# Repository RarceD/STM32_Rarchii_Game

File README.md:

# STM32_Rarchii_Game
This is a simple aproach to the stm32 developer tools and hardware design for one of this low power uC.

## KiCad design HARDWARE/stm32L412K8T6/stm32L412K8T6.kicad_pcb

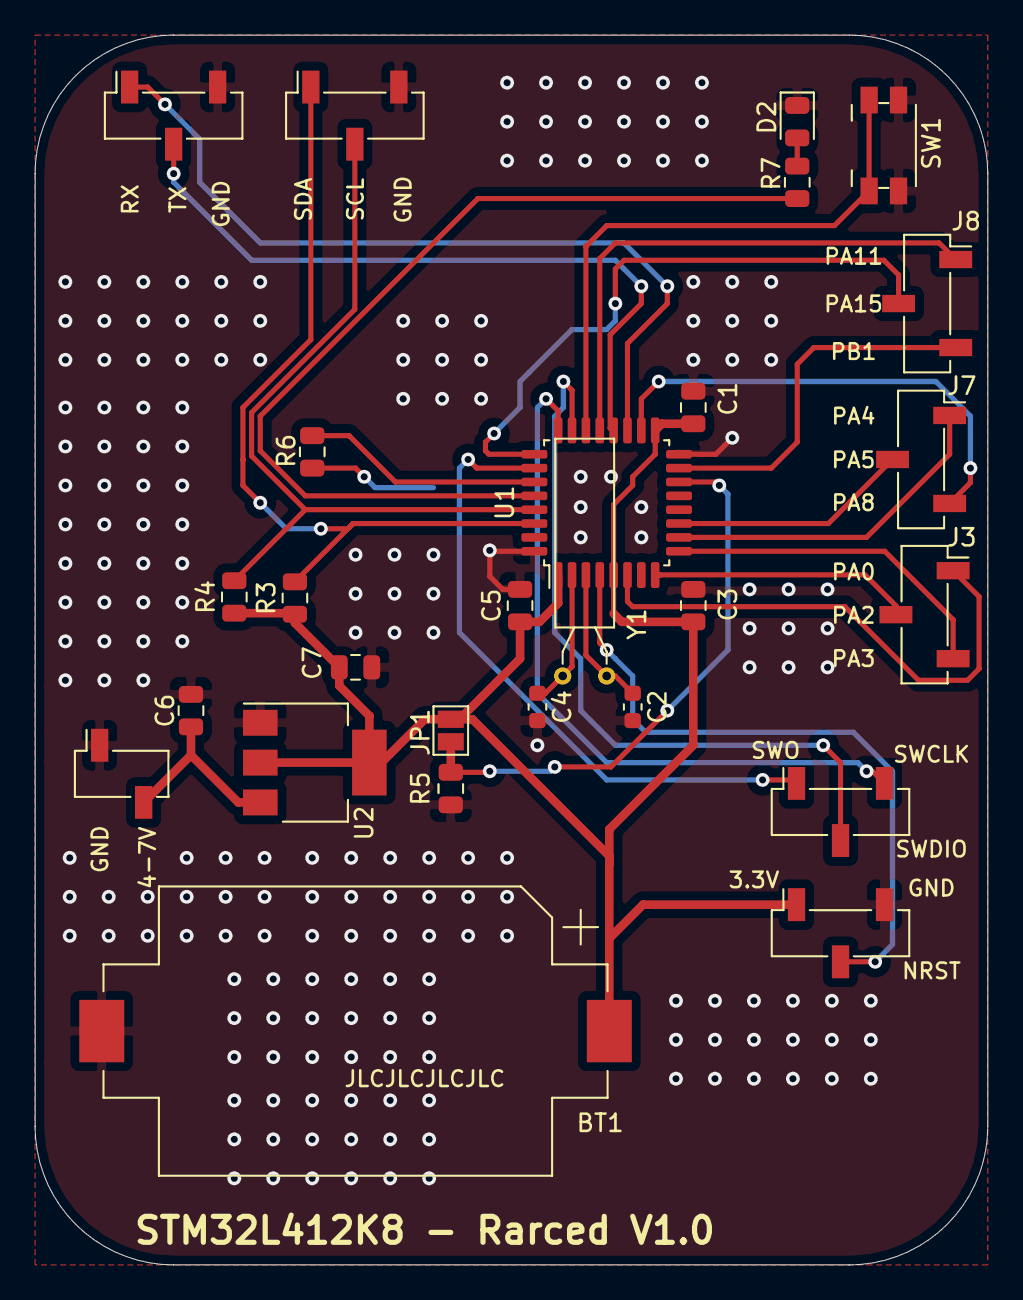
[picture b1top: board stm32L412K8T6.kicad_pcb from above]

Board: 2 copper layers, 55.0 x 71.0 mm, 28 parts (1 on the bottom side), 28 nets.

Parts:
BT1: Battery_Cell; BatteryHolder_Keystone_1060_1x2032
C1, C3, C5: 0.1u; C_0805_2012Metric
C2, C4: 2.7p; C_0603_1608Metric
C6, C7: 10u; C_0805_2012Metric
D1, D2: LED; LED_0805_2012Metric
J1: Conn_01x02; PinSocket_1x02_P2.54mm_Vertical_SMD_Pin1Right
J2, J3, J4, J5, J6, J7, J8: Conn_01x03_Male; PinSocket_1x03_P2.54mm_Vertical_SMD_Pin1Right
JP1: SolderJumper_2_Open; SolderJumper-2_P1.3mm_Open_Pad1.0x1.5mm
R3, R4: 2.2k; R_0805_2012Metric
R5: R; R_0805_2012Metric
R6, R7: 1k; R_0805_2012Metric
SW1: SW_Push; Panasonic_EVQPUJ_EVQPUA
U1: STM32L011K3Tx; LQFP-32_7x7mm_P0.8mm
U2: AMS1117-3.3; SOT-223-3_TabPin2
Y1: Crystal; Crystal_AT310_D3.0mm_L10.0mm_Horizontal

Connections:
14_OSC_IN: C4.1, U1.2, Y1.2
15_OSC_OUT: C2.1, U1.3, Y1.1
+3V3: BT1.1, C1.1, C3.1, C5.1, C7.1, J4.1, JP1.1, R3.1, R4.1, U1.1, U1.5, U1.17, U2.2
BOOT0: JP1.2, R5.1, U1.14
BUTTON: SW1.1, U1.22
GND: BT1.2, C1.2, C2.2, C3.2, C4.2, C5.2, C6.2, C7.2, D1.1, D2.1, J1.1, J2.3, J4.3, J5.3, R5.2, SW1.2, U1.16, U1.32, U2.1
INPUT: C6.1, J1.2, U2.3
LED_GREEN: R7.1, U1.28
LED_RED: R6.1, U1.27
NRST: J4.2, U1.4
unnamed: D1.2, R6.2
unnamed: D2.2, R7.2
PA0: J3.1, U1.6
PA2: J3.2, U1.8
PA3: J3.3, U1.9
PA4: J7.1, U1.10
PA5: J7.2, U1.11
PA8: J7.3, U1.18
PA11: J8.1, U1.21
PA15: J8.2, U1.25
PB1: J8.3, U1.15
RX: J2.1, U1.19
SCL: J5.2, R4.2, U1.29
SDA: J5.1, R3.2, U1.30
SWCLK: J6.3, U1.24
SWDIO: J6.2, U1.23
SWO: J6.1, U1.26
TX: J2.2, U1.20

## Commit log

2020-12-31 oled game project
2020-12-31 add buttons and leds to configuration
2020-12-31 create bitmap image but not show properly
2021-01-01 images using LCD image converter
2021-01-01 timer 2 configure, running at 60MHz the device
2021-01-02 capitals game 1 and structs for hold the response
2021-01-03 selected menu in game1 and counter the points
2021-01-03 implement game 4 logic
2021-01-03 create a gameplay logic .c .h to tidy the code
2021-01-04 tool for monochrome images
2021-01-04 create the second game on gameplay_logic
2021-01-04 math game also integrated
2021-01-07 save the pts of the children games on internal flash
2021-01-08 fail in processing gerber, create a new board
